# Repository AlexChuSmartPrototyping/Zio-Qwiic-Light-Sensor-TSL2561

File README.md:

# Zio Qwiic Light Sensor (TSL2561)

> This product can be available for purchase [here](https://www.smart-prototyping.com/Zio-Qwiic-Light-Sensor-TSL2561).

#### Description

This inexpensive precision light sensor is, although compact in size, is robust enough to output the exact luminance rate for visible light (Approximates Human Eye Response), invisible light (IR), and full light (both visible and invisible light) from up to 0.1 - 40,000+ lux on the fly! 

With [Qwiic](https://www.smart-prototyping.com/Qwiic.html) installed you can effortlessly prototype your projects without soldering and complicated wiring. We also added I2C pins for connecting to modules outside the qwiic domain.

Especially reliable for projects and applications involving Street light controlling system, monitoring luminosity of the living environment, or simply doing research on light brightness. 

All in all, if you need a light sensor in a project, this is definitely the right choice!

#### Specification

* Dynamic range (Lux): 0.1 to 40,000 Lux
* Voltage range: 2.7-3.6V
* Interface: I2C
* I2C Address: 0x39 (Default), 0x29, 0x49, selectable with jumpers
* Module dimension: 14.4x 25.4mm
* Weight: 1.3g

#### Links

* [PCB Source file and Gerber file](https://github.com/ZIOCC/Zio-Qwiic-Light-Sensor-TSL2561)
* [PCB Schematic](https://github.com/ZIOCC/Zio-Qwiic-Light-Sensor-TSL2561/blob/master/Zio%20Qwiic%20Light%20Sensor%20TSL2561%20Schematic%20PDF.pdf)
* [Demo Code and library](https://github.com/adafruit/TSL2561-Arduino-Library)

> ###### About Zio
> Zio is a new line of open sourced, compact, and grid layout boards, fully integrated for Arduino and Qwiic ecosystem. Designed ideally for wearables, robotics, small-space limitations or other on the go projects. Check out other awesome Zio products [here](https://www.smart-prototyping.com/Zio).

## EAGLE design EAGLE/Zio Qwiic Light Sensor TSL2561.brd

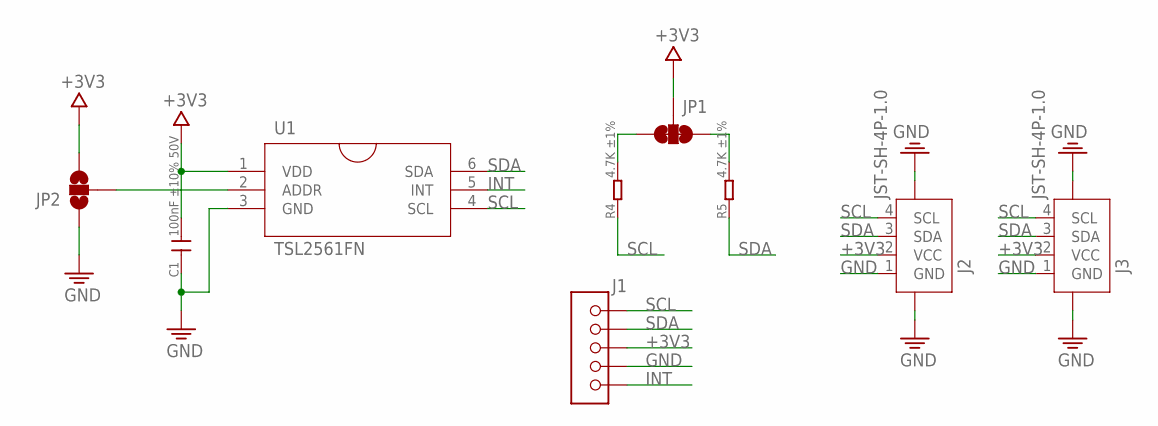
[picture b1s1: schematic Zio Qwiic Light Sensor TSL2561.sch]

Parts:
C1: 100nF ±10% 50V; C0603
J1: HEADER-5P-2.54; 5P-2.54
J2, J3: JST-SH-4P-1.0; JST-SH-4P
JP1: SMT-JUMPER_3_2-NC_TRACE
JP2: JUMPER-SMT_3_2-NC_PASTE_NOCREM; SMT-JUMPER_3_2-NC_PASTE_SILK_NOCREM
R4, R5: 4.7K ±1%; R0603
U1: TSL2561FN; FN6

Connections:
+3V3: C1.2, J1.3, J2.2 (VCC), J3.2 (VCC), JP1.2, JP2.3, U1.1 (VDD)
GND: C1.1, J1.4, J2.1 (GND), J2.NC1 (5), J2.NC2 (6), J3.1 (GND), J3.NC1 (5), J3.NC2 (6), JP2.1, U1.3 (GND)
INT: J1.5, U1.5 (INT)
unnamed: JP2.2, U1.2 (ADDR)
unnamed: JP1.3, R4.2
unnamed: JP1.1, R5.2
SCL: J1.1, J2.4 (SCL), J3.4 (SCL), R4.1, U1.4 (SCL)
SDA: J1.2, J2.3 (SDA), J3.3 (SDA), R5.1, U1.6 (SDA)

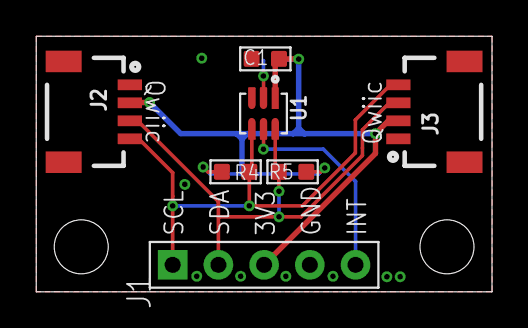
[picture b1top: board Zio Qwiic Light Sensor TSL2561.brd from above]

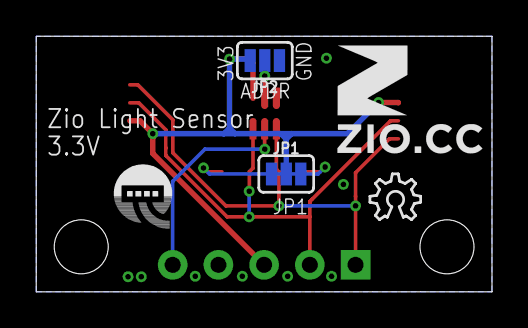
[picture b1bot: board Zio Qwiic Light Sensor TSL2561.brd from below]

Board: 2 copper layers, 25.3 x 14.2 mm, 12 parts (5 on the bottom side), 8 nets.

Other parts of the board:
U$4: 6MM
U$5: QWIIC-LOGO-BASIC
U$6: OSHW_6X100_NOTEXT
